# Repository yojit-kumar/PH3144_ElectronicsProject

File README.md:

# Precision Closed-Loop AC Power Controller using PID Algorithm

**Course:** PH3144 Electronics-I with Lab

**Status:** Finished (with incomplete code implementation)

A project to design and build a closed-loop AC power controller using a PID algorithm to deliver a precise, stable power output to a load.

## Team Members & Responsibilities
* **Uday Pratap Bais (20231267):** Hardware Lead (Electrical), Design Lead.
* **Yash Dadhwal (20231287):** Software Lead (Algorithm), Testing, Software Integration.
* **Yojit Kumar (20231289):** Hardware Lead (Electronics), Documentation Lead.

## Project Structure
* **/docs:** Contains all project documentation, including the report, component datasheets, and images.
* **/hardware:** Contains hardware design files (schematics, PCB layouts from KiCad).
* **/src:** Contains all Arduino source code, organized by testing phase.
* **/dump:** Put anything and everything we find before the finalizing of the project, It may later get sorted and moved to the relavant folders.

## Getting Started
1.  Clone the repository: `git clone https://github.com/yojit-kumar/PH3144_ElectronicsProject`
2.  Install the required Arduino libraries:
    * `EmonLib`
    * `LiquidCrystal_I2C`
    * `Adafruit_ADS1X15`
3. Use the calibiration codes in the `src/` directory to calibirate the measurement components
4. Run the test codes from the same directory.
---

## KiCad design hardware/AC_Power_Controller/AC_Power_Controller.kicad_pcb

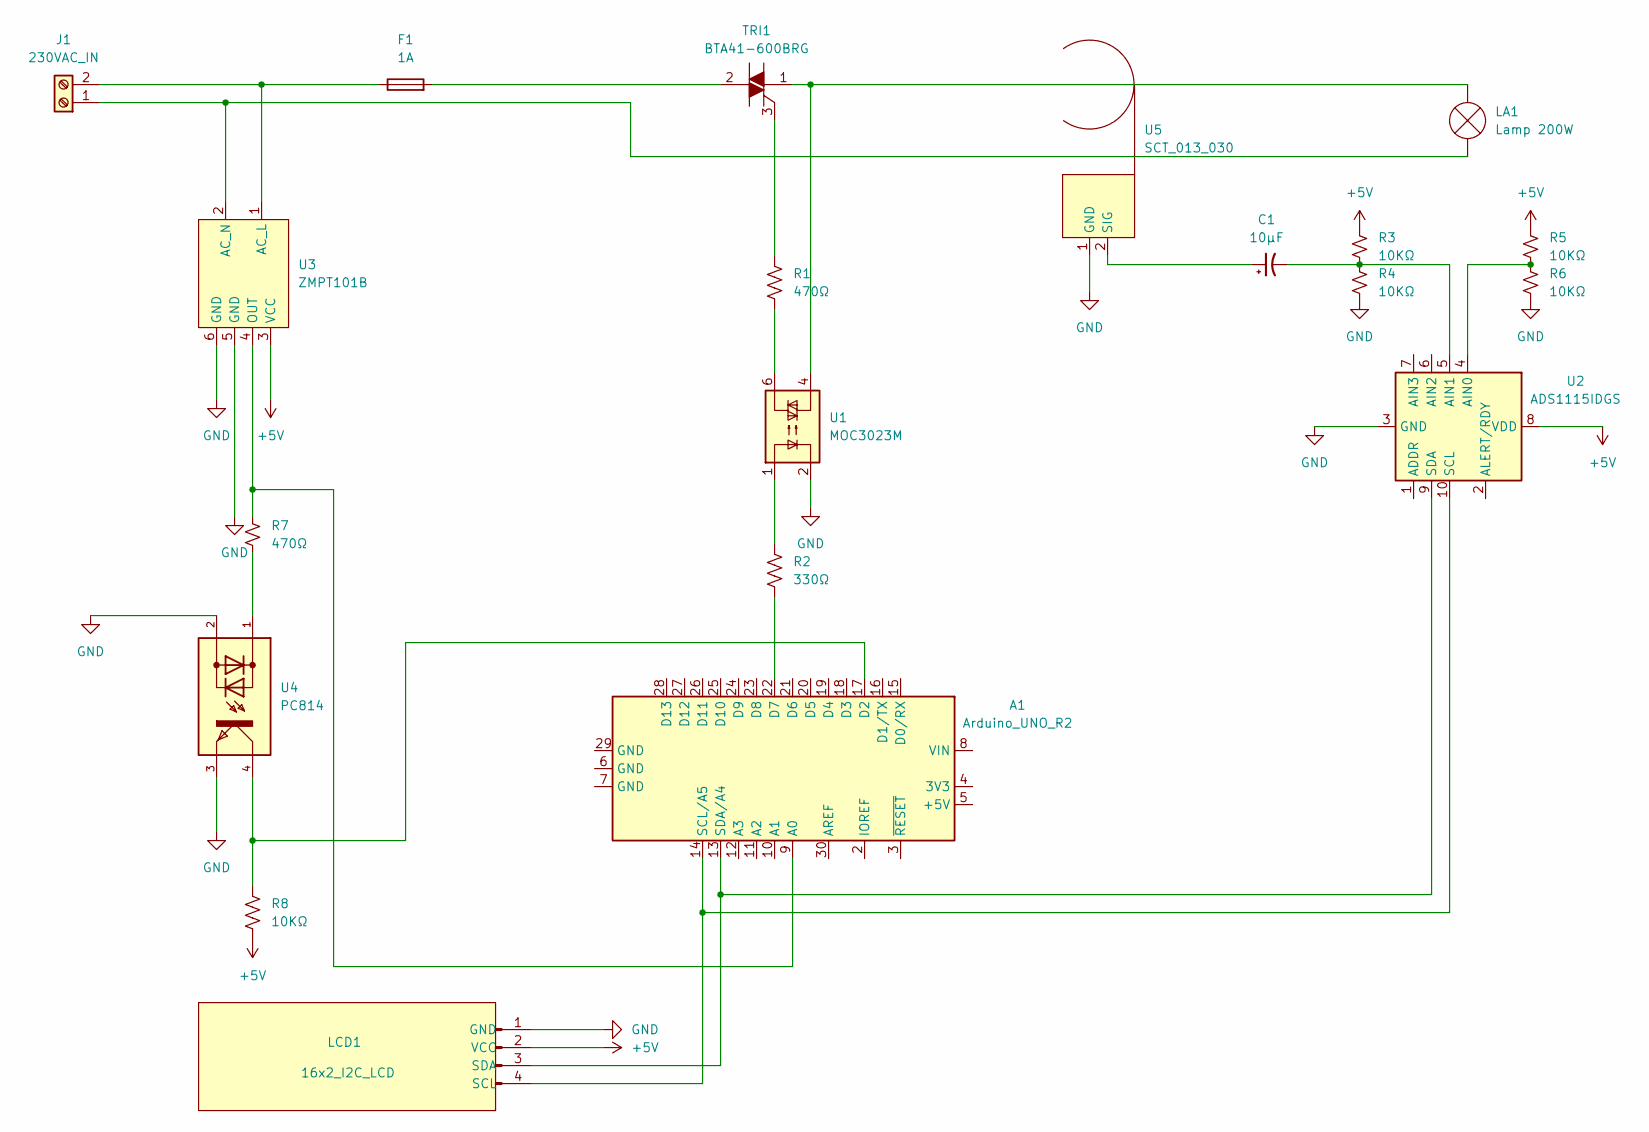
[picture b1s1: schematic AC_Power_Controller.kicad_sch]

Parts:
A1: Arduino_UNO_R2
C1: 10µF; PinHeader_1x06_P2.54mm_Vertical
F1: 1A; FuseHolder_Blade_ATO_Littelfuse_FLR_178.6165
J1: 230VAC_IN; PinHeader_1x02_P2.54mm_Vertical
LA1: Lamp 200W; PinHeader_1x02_P2.54mm_Vertical
LCD1: 16x2_I2C_LCD; PinHeader_1x04_P2.54mm_Vertical
R1, R7: 470Ω; R_Axial_DIN0204_L3.6mm_D1.6mm_P5.08mm_Horizontal
R2: 330Ω; R_Axial_DIN0204_L3.6mm_D1.6mm_P5.08mm_Horizontal
R3, R4, R5, R6, R8: 10KΩ; R_Axial_DIN0204_L3.6mm_D1.6mm_P5.08mm_Horizontal
TRI1: BTA41-600BRG; TOP-3_Vertical_Insulated; MPN BTA41-600BRG; Digi-Key_PN 497-2431-5-ND
U1: MOC3023M; DIP-6_W7.62mm
U2: ADS1115IDGS; TSSOP-10_3x3mm_P0.5mm
U3: ZMPT101B; PinHeader_1x06_P2.54mm_Vertical
U4: PC814; DIP-4_W10.16mm
U5: SCT_013_030; PinHeader_1x02_P2.54mm_Vertical

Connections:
+5V: LCD1.2 (VCC), R3.1, R5.1, R8.2, U2.8 (VDD), U3.3 (VCC)
GND: LCD1.1 (GND), R4.2, R6.2, U1.2, U2.3 (GND), U3.5 (GND), U3.6 (GND), U4.2, U4.3, U5.1 (GND)
unnamed: A1.9 (A0), R7.1, U3.4 (OUT)
unnamed: A1.17 (D2), R8.1, U4.4
unnamed: A1.22 (D7), R2.2
unnamed: A1.14 (SCL/A5), LCD1.4 (SCL), U2.10 (SCL)
unnamed: A1.13 (SDA/A4), LCD1.3 (SDA), U2.9 (SDA)
unnamed: J1.1, LA1.1 (-), U3.2 (AC_N)
unnamed: F1.1, J1.2, U3.1 (AC_L)
unnamed: LA1.2 (+), TRI1.1 (A1), U1.4
unnamed: R1.2, U1.6
unnamed: R2.1, U1.1
unnamed: R7.2, U4.1
unnamed: F1.2, TRI1.2 (A2)
unnamed: R1.1, TRI1.3 (G)
unnamed: R5.2, R6.1, U2.4 (AIN0)
unnamed: C1.2, R3.2, R4.1, U2.5 (AIN1)
unnamed: C1.1, U5.2 (SIG)

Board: 2 copper layers, 20 parts (0 on the bottom side), 18 nets, no tracks yet.

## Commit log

2025-10-21 Create PID code
    Bhaiyo is code ka use kare,
2025-10-21 Update PID code
2025-10-23 test_code
2025-10-29 prototyping done, test code uploaded. New IC datasheet added
2025-10-31 added schematics
2025-11-01 minors changes to schematics
2025-11-01 corrections to schematics
2025-11-06 final_codes
2025-11-06 schematic corrections
2025-11-07 done, maybe
2025-11-12 Add phase-angle PID control with ADS1115
    Implement phase-angle PID control with ADS1115 and LCD display for voltage and current measurements.
2025-11-13 done, please, final code with fixes, looper & dimmer works
2025-11-18 working final_report
2025-11-18 gotcha
2025-11-20 final_report_submit
2026-03-20 final commit
2026-04-06 file left to push
